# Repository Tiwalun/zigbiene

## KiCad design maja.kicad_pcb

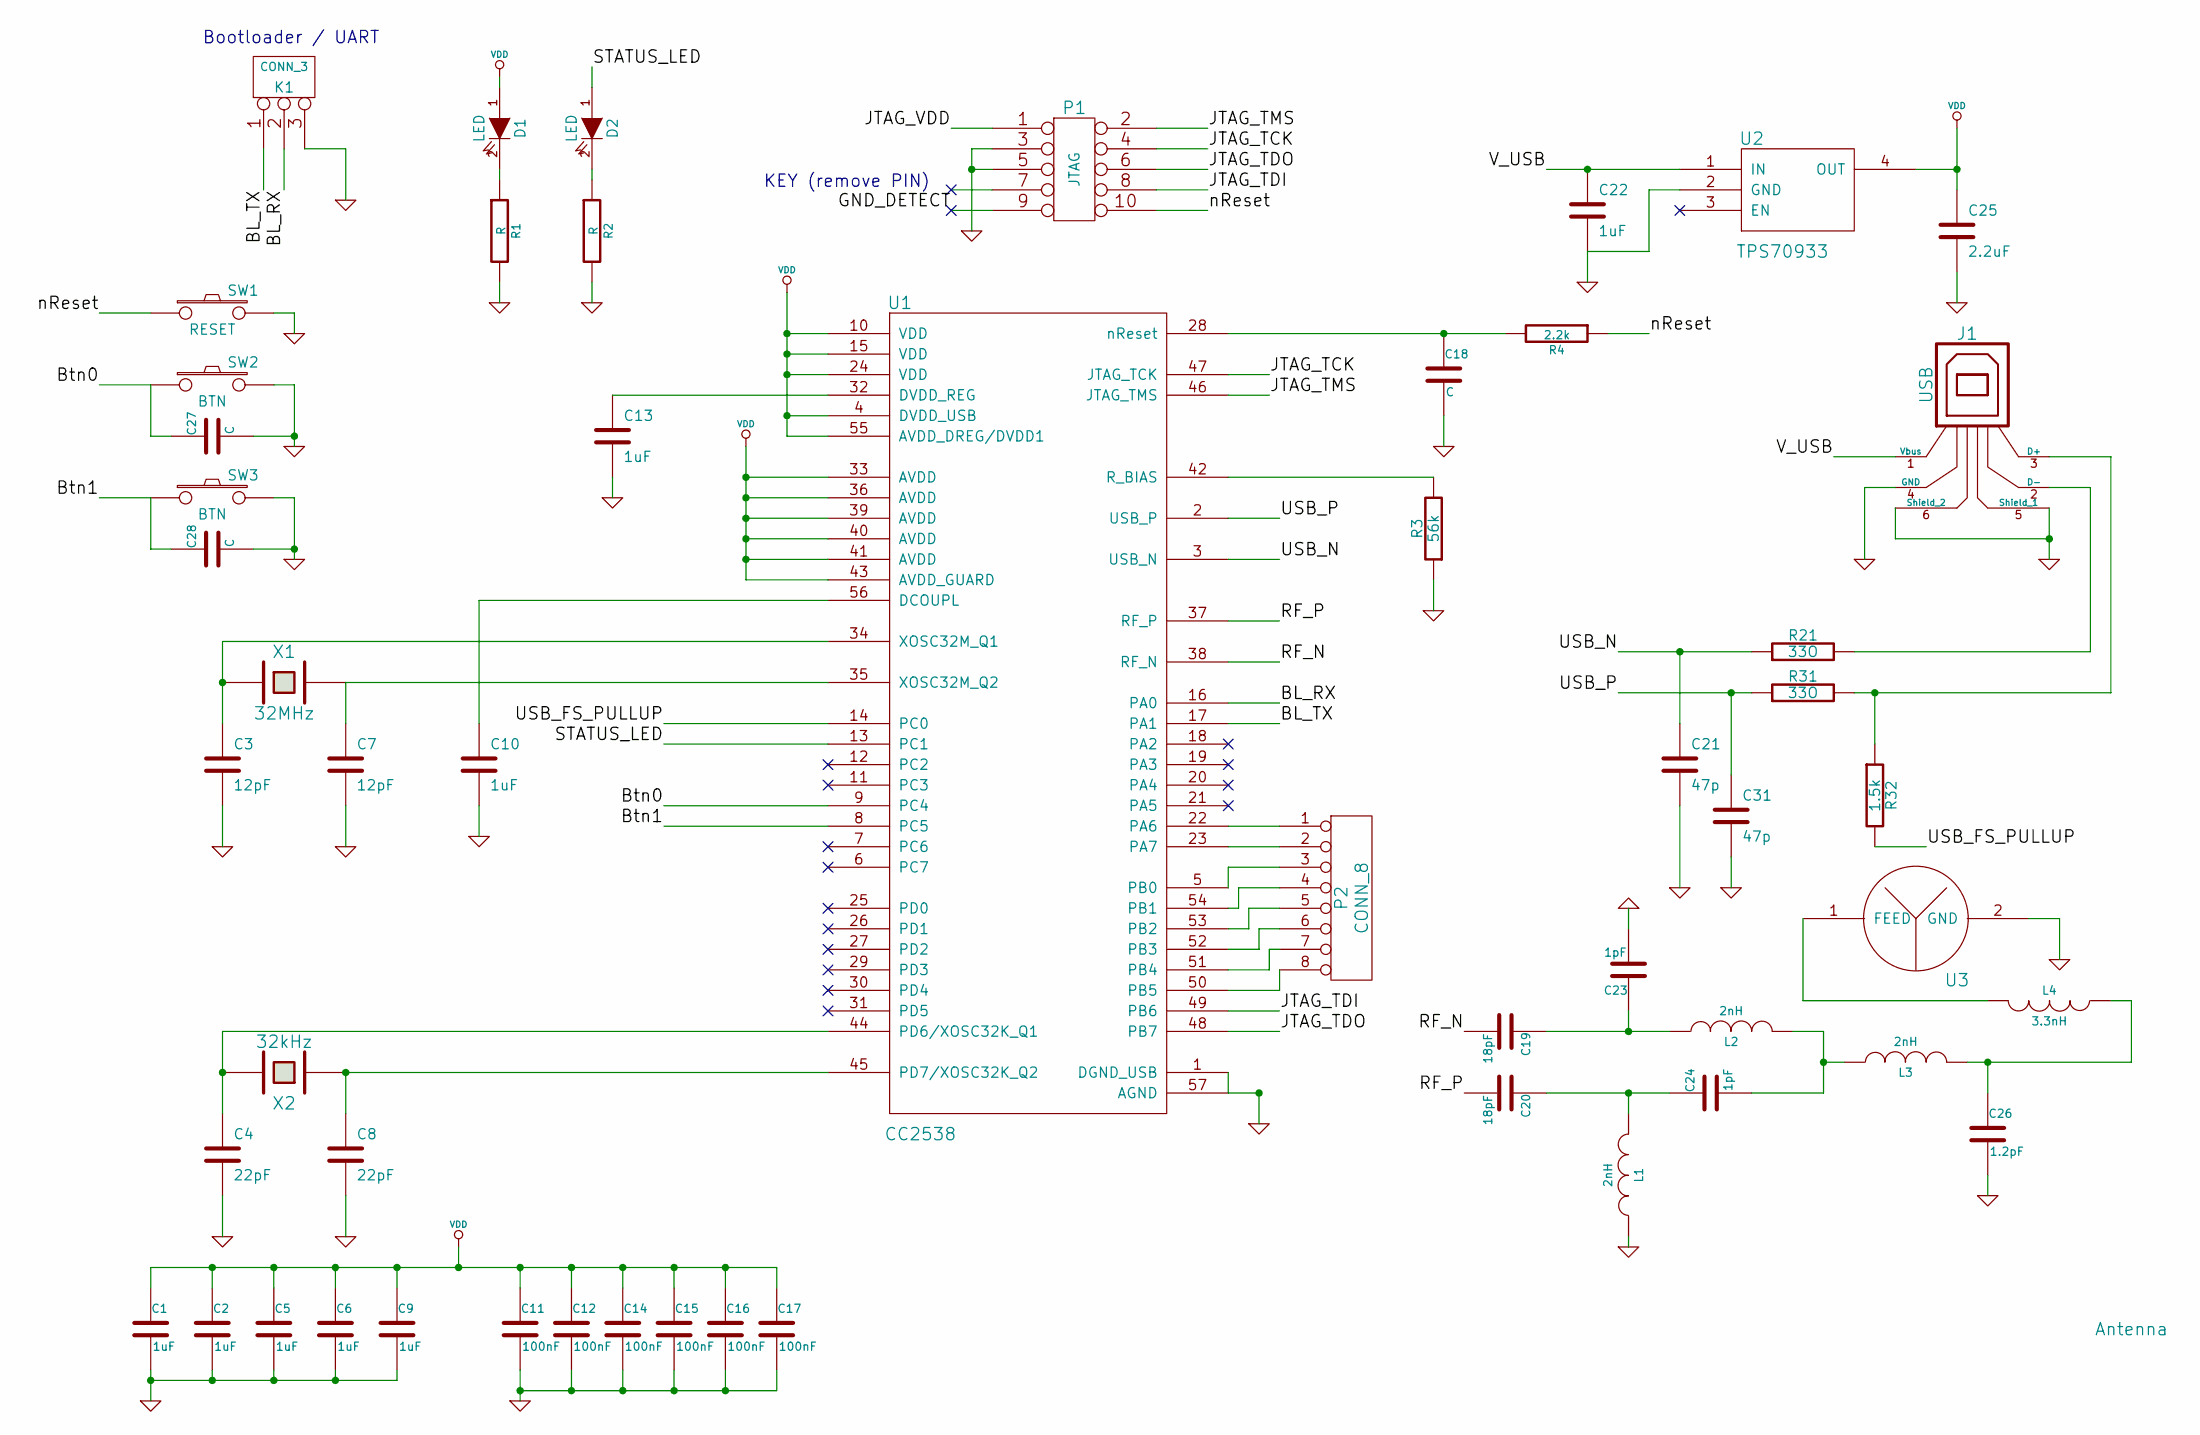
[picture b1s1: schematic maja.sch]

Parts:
C1, C2, C5, C6, C9, C10, C13, C22: 1uF
C3, C7: 12pF
C4, C8: 22pF
C11, C12, C14, C15, C16, C17: 100nF
C18, C27, C28: C
C19, C20: 18pF
C21, C31: 47p
C23, C24: 1pF
C25: 2.2uF
C26: 1.2pF
D1, D2: LED
J1: USB
K1: CONN_3
L1, L2, L3: 2nH
L4: 3.3nH
P1: JTAG
P2: CONN_8
R1, R2: R
R3: 56k
R4: 2.2k
R21, R31: 33O
R32: 1.5k
SW1: RESET
SW2, SW3: BTN
U1: CC2538
U2: TPS70933
U3: Antenna
X1: 32MHz
X2: 32kHz

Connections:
/BL_RX: K1.2 (PM), U1.16 (PA0)
/BL_TX: K1.1, U1.17 (PA1)
/Btn0: C27.1, SW2.1, U1.9 (PC4)
/Btn1: C28.1, SW3.1, U1.8 (PC5)
/GND_DETECT: P1.9
/JTAG_TCK: P1.4, U1.47 (JTAG_TCK)
/JTAG_TDI: P1.8, U1.49 (PB6)
/JTAG_TDO: P1.6, U1.48 (PB7)
/JTAG_TMS: P1.2, U1.46 (JTAG_TMS)
/JTAG_VDD: P1.1
/RF_N: C19.2, U1.38 (RF_N)
/RF_P: C20.2, U1.37 (RF_P)
/STATUS_LED: D2.1 (A), U1.13 (PC1)
/USB_FS_PULLUP: R32.2, U1.14 (PC0)
/USB_N: C21.1, R21.1, U1.3 (USB_N)
/USB_P: C31.1, R31.1, U1.2 (USB_P)
/V_USB: C22.1, J1.1 (Vbus), U2.1 (IN)
/nReset: P1.10, R4.1, SW1.1
GND: C1.2, C2.2, C3.2, C4.2, C5.2, C6.2, C7.2, C8.2, C9.2, C10.2, C11.2, C12.2, C13.2, C14.2, C15.2, C16.2, C17.2, C18.2, C21.2, C22.2, C23.2, C25.2, C26.2, C27.2, C28.2, C31.2, J1.4 (GND), J1.5 (Shield_1), J1.6 (Shield_2), K1.3, L1.1, P1.3, P1.5, R1.2, R2.2, R3.1, SW1.2, SW2.2, SW3.2, U1.1 (DGND_USB), U1.57 (AGND), U2.2 (GND), U3.2 (GND)
unnamed: C3.1, U1.34 (XOSC32M_Q1), X1.1
unnamed: C4.1, U1.44 (PD6/XOSC32K_Q1), X2.2
unnamed: C7.1, U1.35 (XOSC32M_Q2), X1.2
unnamed: C8.1, U1.45 (PD7/XOSC32K_Q2), X2.1
unnamed: C10.1, U1.56 (DCOUPL)
unnamed: C13.1, U1.32 (DVDD_REG)
unnamed: C18.1, R4.2, U1.28 (nReset)
unnamed: C19.1, C23.1, L2.1
unnamed: C20.1, C24.1, L1.2
unnamed: C24.2, L2.2, L3.1
unnamed: C26.1, L3.2, L4.1
unnamed: D1.2 (K), R1.1
unnamed: D2.2 (K), R2.1
unnamed: J1.2 (D-), R21.2
unnamed: J1.3 (D+), R31.2, R32.1
unnamed: L4.2, U3.1 (FEED)
unnamed: P2.1, U1.22 (PA6)
unnamed: P2.2, U1.23 (PA7)
unnamed: P2.3, U1.5 (PB0)
unnamed: P2.4, U1.54 (PB1)
unnamed: P2.5, U1.53 (PB2)
unnamed: P2.6, U1.52 (PB3)
unnamed: P2.7, U1.51 (PB4)
unnamed: P2.8, U1.50 (PB5)
unnamed: R3.2, U1.42 (R_BIAS)
VDD: C1.1, C2.1, C5.1, C6.1, C9.1, C11.1, C12.1, C14.1, C15.1, C16.1, C17.1, C25.1, D1.1 (A), U1.4 (DVDD_USB), U1.10 (VDD), U1.15 (VDD), U1.24 (VDD), U1.33 (AVDD), U1.36 (AVDD), U1.39 (AVDD), U1.40 (AVDD), U1.41 (AVDD), U1.43 (AVDD_GUARD), U1.55 (AVDD_DREG/DVDD1), U2.4 (OUT)

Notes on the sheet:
Bootloader / UART
KEY (remove PIN)

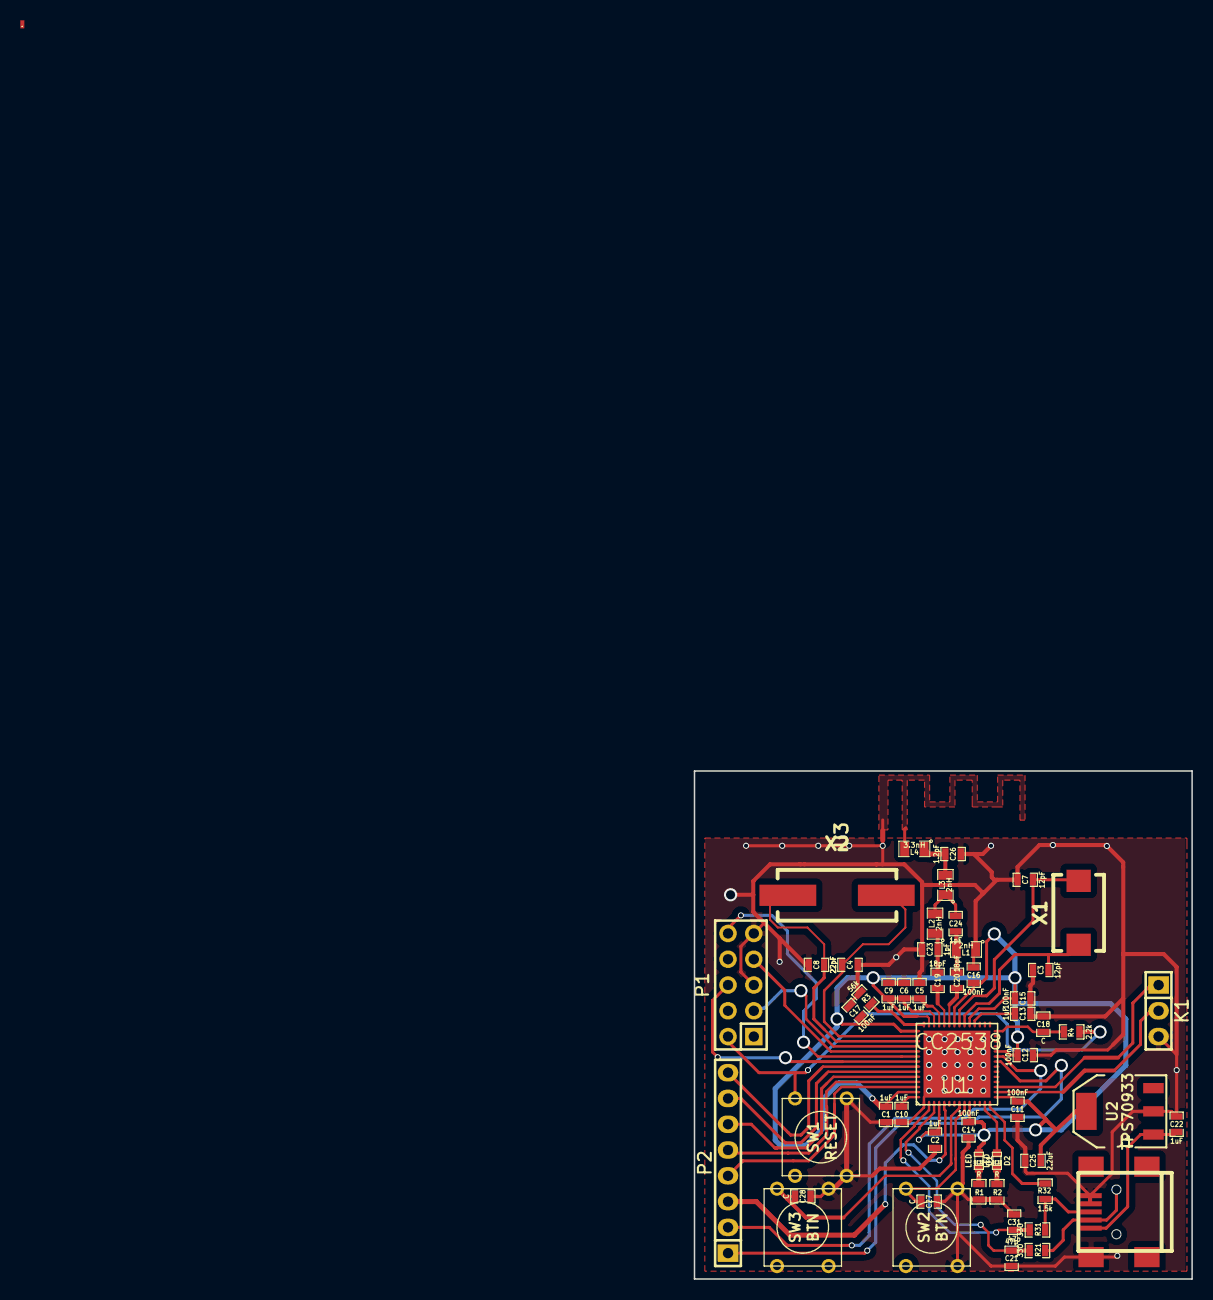
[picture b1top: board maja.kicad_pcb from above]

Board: 2 copper layers, 49.0 x 50.0 mm, 55 parts (0 on the bottom side), 43 nets.

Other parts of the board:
STUB: VAL**; STUB

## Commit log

2014-03-15 Started with basic PCB layout. Footprints must be checked again! I just choose one to be able to do a prelimary placement
2014-03-17 Started with routing, added two missing JTAG signals and corrected one library error
2014-03-18 Small changes, some wires were mangled..
2014-03-20 Sync
2014-03-21 More layouting...
2014-03-21 Finished routing more or less, it is a real pain and uses much too much vias. We have to optimize this if possible
2014-03-23 Ignore temporary Kicad file
2014-03-23 Add antenna
2014-03-23 Get rid of 2 vias
2014-04-15 Change quartz
2014-04-28 Added copper fills, changed net tie so that antenna now looks okay
2014-04-29 Add blind vias under SMD
2014-04-29 Resize pcb
2014-04-29 So far so good
